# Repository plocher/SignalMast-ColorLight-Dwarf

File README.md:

# SignalMast-Dwarf
## License: CERN Open Hardware Licence v1.2

Low cost Signal Mast - single high head 3-lamp Color Light - N scale

SP style color light signal heads

Color-light signals consist of three bulbs shining through three lenses, or "roundels," one each red, yellow, and green. The lights are grouped vertically with green at the top.

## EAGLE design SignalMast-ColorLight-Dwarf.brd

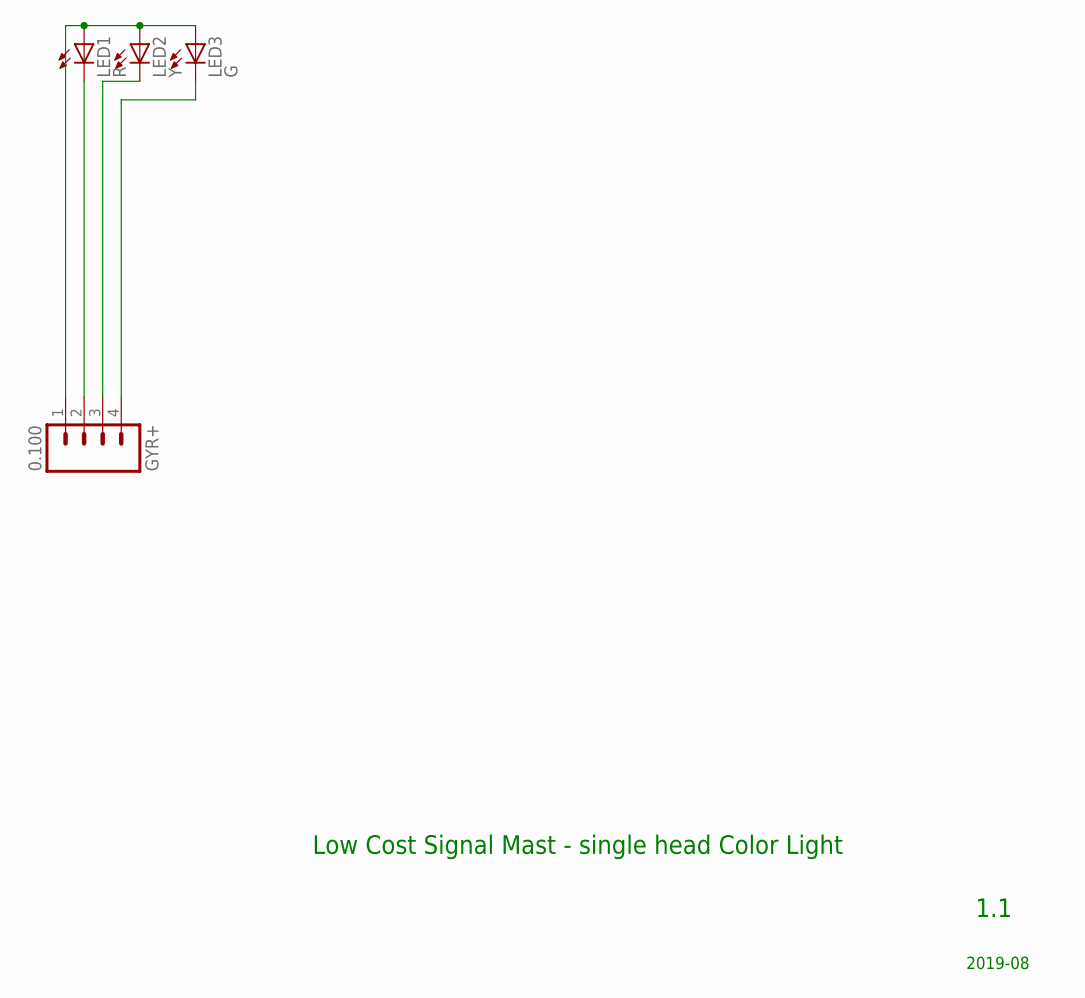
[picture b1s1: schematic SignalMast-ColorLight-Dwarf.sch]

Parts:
GYR+: 0.100; 1X04_LOCK
LED1: R; 0603-LED
LED2: Y; 0603-LED
LED3: G; 0603-LED

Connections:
BG: GYR+.4, LED3.C
BR: GYR+.2, LED1.C
BV+: GYR+.1, LED1.A, LED2.A, LED3.A
BY: GYR+.3, LED2.C

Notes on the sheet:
1.1
2019-08
Low Cost Signal Mast - single head Color Light

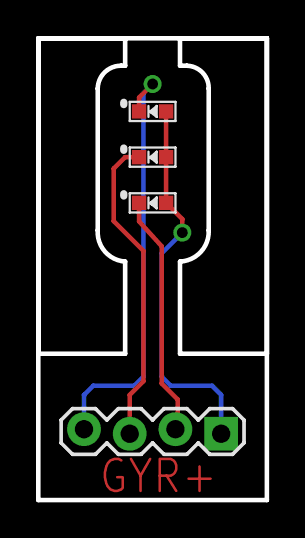
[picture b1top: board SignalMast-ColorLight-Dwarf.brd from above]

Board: 2 copper layers, 12.7 x 25.7 mm, 4 parts (0 on the bottom side), 4 nets.

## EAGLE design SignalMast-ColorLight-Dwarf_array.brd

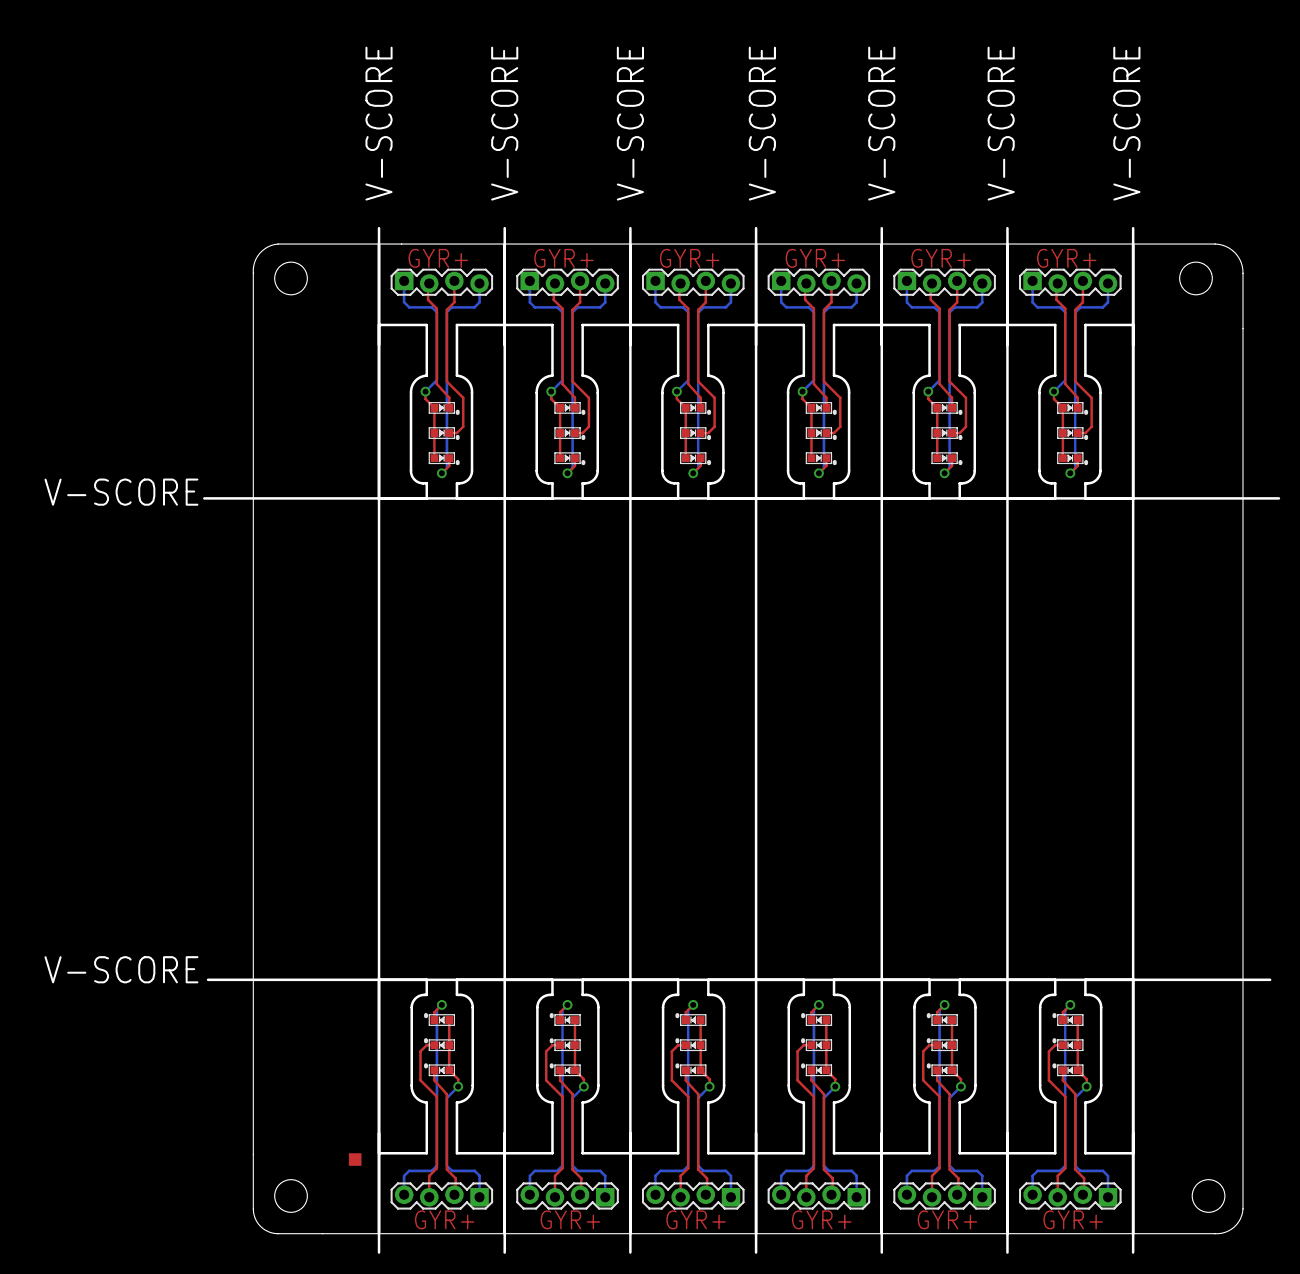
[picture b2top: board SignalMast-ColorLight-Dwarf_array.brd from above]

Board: 2 copper layers, 108.6 x 103.5 mm, 49 parts (0 on the bottom side), 48 nets.

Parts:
BOARD1: BOARD; BOARD-SEEED10X10-NOHOLES
GYR+, GYR+1, GYR+2, GYR+3, GYR+4, GYR+5, GYR+6, GYR+7, GYR+8, GYR+9, GYR+10, GYR+11: 0.100; 1X04_LOCK
LED1, LED4, LED7, LED10, LED13, LED16, LED19, LED22, LED25, LED28, LED31, LED34: R; 0603-LED
LED2, LED5, LED8, LED11, LED14, LED17, LED20, LED23, LED26, LED29, LED32, LED35: Y; 0603-LED
LED3, LED6, LED9, LED12, LED15, LED18, LED21, LED24, LED27, LED30, LED33, LED36: G; 0603-LED

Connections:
BG: GYR+.4, LED3.C
BG1: GYR+1.4, LED6.C
BG2: GYR+2.4, LED9.C
BG3: GYR+3.4, LED12.C
BG4: GYR+4.4, LED15.C
BG5: GYR+5.4, LED18.C
BG6: GYR+6.4, LED21.C
BG7: GYR+7.4, LED24.C
BG8: GYR+8.4, LED27.C
BG9: GYR+9.4, LED30.C
BG10: GYR+10.4, LED33.C
BG11: GYR+11.4, LED36.C
BR: GYR+.2, LED1.C
BR1: GYR+1.2, LED4.C
BR2: GYR+2.2, LED7.C
BR3: GYR+3.2, LED10.C
BR4: GYR+4.2, LED13.C
BR5: GYR+5.2, LED16.C
BR6: GYR+6.2, LED19.C
BR7: GYR+7.2, LED22.C
BR8: GYR+8.2, LED25.C
BR9: GYR+9.2, LED28.C
BR10: GYR+10.2, LED31.C
BR11: GYR+11.2, LED34.C
BV+: GYR+.1, LED1.A, LED2.A, LED3.A
BV+1: GYR+1.1, LED4.A, LED5.A, LED6.A
BV+2: GYR+2.1, LED7.A, LED8.A, LED9.A
BV+3: GYR+3.1, LED10.A, LED11.A, LED12.A
BV+4: GYR+4.1, LED13.A, LED14.A, LED15.A
BV+5: GYR+5.1, LED16.A, LED17.A, LED18.A
BV+6: GYR+6.1, LED19.A, LED20.A, LED21.A
BV+7: GYR+7.1, LED22.A, LED23.A, LED24.A
BV+8: GYR+8.1, LED25.A, LED26.A, LED27.A
BV+9: GYR+9.1, LED28.A, LED29.A, LED30.A
BV+10: GYR+10.1, LED31.A, LED32.A, LED33.A
BV+11: GYR+11.1, LED34.A, LED35.A, LED36.A
BY: GYR+.3, LED2.C
BY1: GYR+1.3, LED5.C
BY2: GYR+2.3, LED8.C
BY3: GYR+3.3, LED11.C
BY4: GYR+4.3, LED14.C
BY5: GYR+5.3, LED17.C
BY6: GYR+6.3, LED20.C
BY7: GYR+7.3, LED23.C
BY8: GYR+8.3, LED26.C
BY9: GYR+9.3, LED29.C
BY10: GYR+10.3, LED32.C
BY11: GYR+11.3, LED35.C

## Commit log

2019-12-07 added graphic
2020-05-04 updated tags
2020-10-05 added missing values
2020-10-06 normalized values
